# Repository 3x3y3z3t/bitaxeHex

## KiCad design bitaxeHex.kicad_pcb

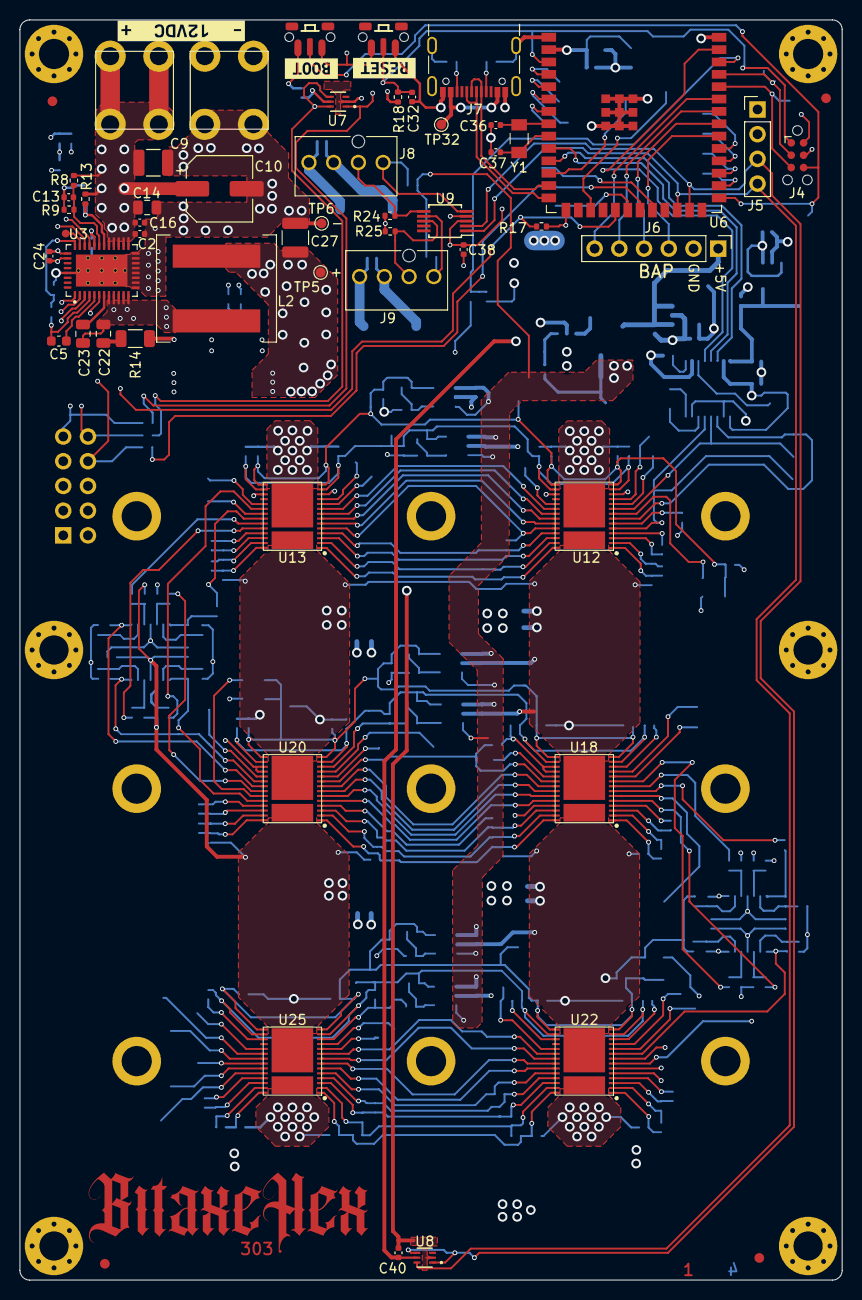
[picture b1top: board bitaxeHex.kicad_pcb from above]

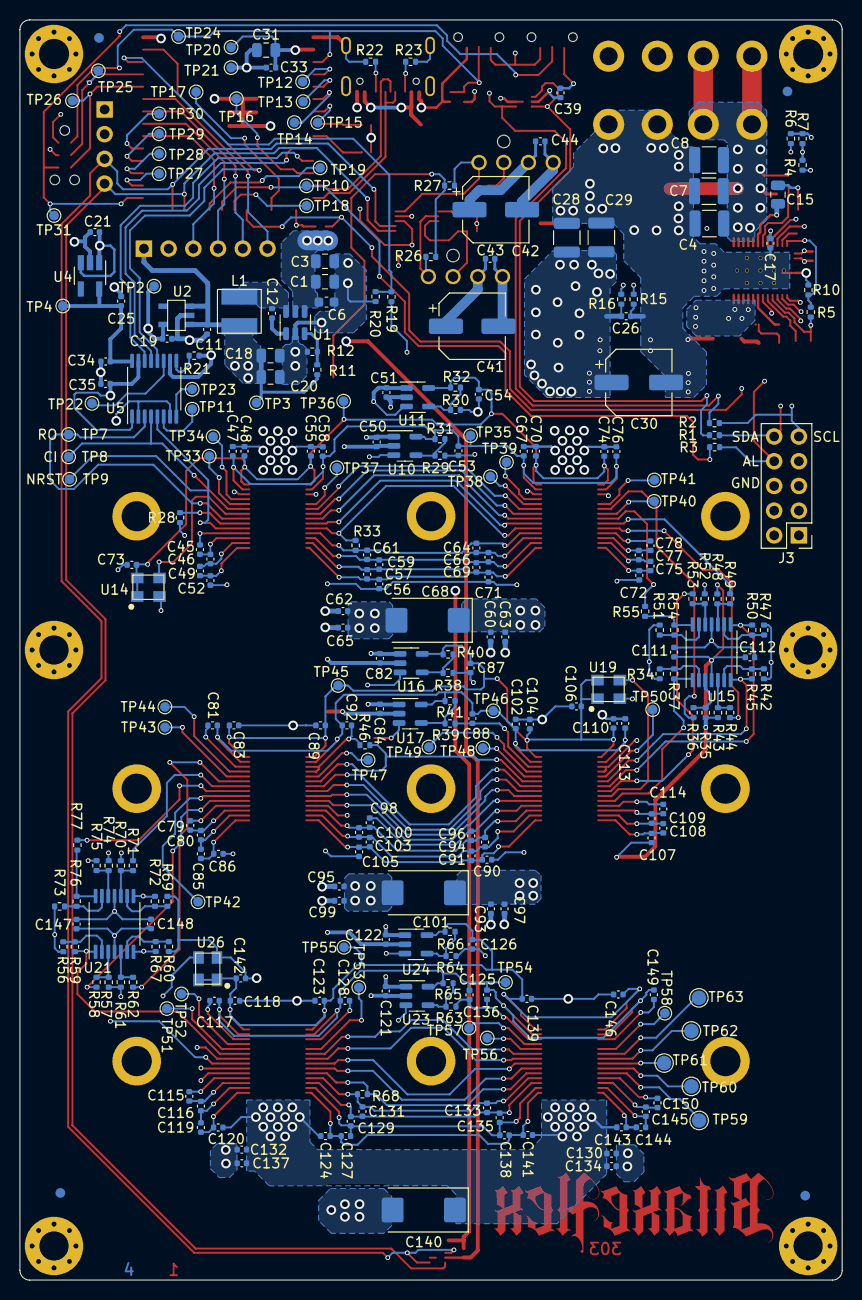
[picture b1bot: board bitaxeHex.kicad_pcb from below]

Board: 4 copper layers, 84.5 x 129.5 mm, 357 parts (283 on the bottom side), 192 nets.

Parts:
C1, C3, C18, C20, C31: 10uF; C_0805_2012Metric
C2: 4.7nF; C_0402_1005Metric
C4, C7, C8, C9: 22uF; C_1210_3225Metric
C5: 1uF; C_0603_1608Metric
C6: 0.1uF; C_0603_1608Metric
C10, C30: 180uF; CP_Elec_6.3x5.9
C11, C19, C21, C25, C32, C45, C46, C47, C48, C49, C52, C53, C54, C55, C56, C57, C58, C59, C61, C63, C64, C65, C66, C67, C69, C70, C71, C72, C74, C75, C76, C77, C78, C79, C80, C81, C83, C85, C86, C87, C88, C89, C90, C91, C92, C94, C96, C97, C98, C99, C100, C102, C103, C104, C105, C107, C108, C109, C110, C112, C113, C114, C115, C116, C117, C118, C119, C120, C123, C124, C125, C126, C127, C128, C129, C131, C133, C134, C135, C136, C137, C138, C139, C141, C143, C144, C145, C146, C148, C149, C150: 1uF; C_0402_1005Metric
C12, C33, C50, C51, C60, C62, C73, C82, C84, C93, C95, C106, C111, C121, C122, C130, C132, C142, C147: 0.1uF; C_0402_1005Metric
C13: 100nF; C_0402_1005Metric
C14, C15: 1uF; C_0805_2012Metric
C16, C26: 2.2nF; C_0402_1005Metric
C17: 4.7uF; C_0402_1005Metric
C22: 1nF; C_0805_2012Metric
C23: 100nF; C_0805_2012Metric
C24: 100pF; C_0402_1005Metric
C27, C28, C29: 47uF; C_1210_3225Metric
C34, C35, C38, C39, C40, C43, C44: 311-3342-1-ND; C_0402_1005Metric
C36, C37: 6.8pF; C_0402_1005Metric
C41, C42: 220uF; CP_Elec_6.3x7.7
C68, C101, C140: 330uF; CP_EIA-7343-31_Kemet-D_Pad2.25x2.55mm_HandSolder
FID1, FID2, FID3, FID4, FID5, FID6, FID7, FID8: Fiducial; Fiducial_1mm_Mask2mm
H1, H2, H3, H4, H5, H6: MountingHole; MountingHole_3mm_Pad_Via
H7, H8, H9, H10, H11, H12, H13, H14, H15: HeatsinkMountingHole; 3.1mm_mounting
HS1: Heatsink; hex-heatsink
J1: Screw Terminal; 7770-screw-terminal
J2: Conn_01x01; 7770-screw-terminal
J3: Conn_02x05_Odd_Even; PinHeader_2x05_P2.54mm_Vertical
J4: TC2030-IDC; Tag-Connect_TC2030-IDC-NL_2x03_P1.27mm_Vertical
J5: Conn_01x04; PinHeader_1x04_P2.54mm_Vertical
J6: Conn_01x06; PinHeader_1x06_P2.54mm_Vertical
J7: USB_C_Receptacle_USB2.0; USB_C_Receptacle_GCT_USB4105-xx-A_16P_TopMnt_Horizontal
J8, J9: Conn_01x04; 470531000
L1: 8.2 uH; 74438357082
L2: 680nH; L_Coilcraft_XAL1010-XXX
R1, R2, R3: 0R; R_0402_1005Metric
R4, R5: 17.8K; R_0402_1005Metric
R6: 10K; R_0402_1005Metric
R7: 31.6K; R_0402_1005Metric
R8: 12.7K; R_0402_1005Metric
R9, R16: 1.37K; R_0402_1005Metric
R10: 26.1K; R_0402_1005Metric
R11, R29, R30, R31, R38, R39, R41, R63, R64, R65: 115k; R_0402_1005Metric
R12, R20: 22.1k; R_0402_1005Metric
R13: 10R; R_0402_1005Metric
R14: 1R; R_1206_3216Metric
R15: 49.9R; R_0402_1005Metric
R17, R18, R26, R27, R28, R35, R36, R43, R44, R48, R49, R52, R53, R57, R58, R61, R62, R70, R71, R74, R75: 10k; R_0402_1005Metric
R19: 7.87k; R_0402_1005Metric
R21: 20k; R_0402_1005Metric
R22, R23: 5.1k; R_0402_1005Metric
R24, R25: 5.6k; R_0402_1005Metric
R32, R40, R66: 402K; R_0402_1005Metric
R33, R46, R68: 2k; R_0402_1005Metric
R34, R37, R42, R45, R47, R50, R51, R54, R55, R56, R59, R60, R67, R69, R72, R73, R76, R77: 1k; R_0402_1005Metric
SW1, SW2: SWITCH-SPST; TL3340-switch
TP1: TestPoint; TestPoint_Pad_D0.8mm
TP2, TP3, TP4, TP5, TP6, TP7, TP8, TP9, TP10, TP11, TP12, TP13, TP14, TP15, TP16, TP17, TP18, TP19, TP20, TP21, TP22, TP23, TP24, TP25, TP26, TP27, TP28, TP29, TP30, TP31, TP32, TP33, TP34, TP35, TP36, TP37, TP38, TP39, TP40, TP41, TP42, TP43, TP44, TP45, TP46, TP47, TP48, TP49, TP50, TP51, TP52, TP53, TP54, TP55, TP56, TP57, TP58: TestPoint; TestPoint_Pad_D1.0mm
TP59, TP60, TP61, TP62, TP63: TestPoint; TestPoint_Pad_D1.5mm
U1: LMR54410; SOT-23-6
U2: RT9080-33GJ5
U3: TPS546D24ARVFR; LQFN40-CLIP
U4: MIC5504; SOT-23-5_HandSoldering
U5: SN74AVC4T774; TSSOP-16_4.4x5mm_P0.65mm
U6: ESP32-S3-WROOM-1; ESP32-S3-WROOM-1U
U7, U8: TMP1075; SOT5X3-6_DRL_TEX
U9: EMC2302; MSOP-10_3x3mm_P0.5mm
U10, U11, U16, U17, U23, U24: AP7331; TSOT-23-5
U12, U13, U22, U25: BM1366_mode1; BM1366
U14, U19, U26: 25MHz; O 25,0-JO32-B-1V3-1-T1-LF
U15, U21: TLV3544; TSSOP-14_4.4x5mm_P0.65mm
U18, U20: BM1366_mode0; BM1366
Y1: 32.768kHz; SC32S-7PF20PPM
kibuzzard-65356D4E: G***; kibuzzard-65356D4E
kibuzzard-65356D5C: G***; kibuzzard-65356D5C
kibuzzard-65978662: G***; kibuzzard-65978662

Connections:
/1V8: C25.1, C34.2, TP4.1, U4.5 (VOUT), U5.16 (VCCA)
/3V3: C19.1, C21.1, C31.1, C33.1, C35.1, C38.1, C39.1, C40.1, J4.2, J5.2, R17.2, R18.1, R24.2, R25.2, TP2.1, TP20.1, U2.5 (VOUT), U4.1 (VIN), U4.3 (EN), U5.1 (DIR1), U5.15 (VCCB), U6.2 (3V3), U6.15 (GPIO3/TOUCH3/ADC1_CH2*), U7.5 (V+), U8.5 (V+), U9.3 (VDD)
/5V: C11.1, C18.1, C20.1, C50.2, C51.2, C82.2, C84.2, C121.2, C122.2, J6.1, L1.2, R11.1, R26.2, R27.2, TP3.1, U2.1 (VIN), U2.3 (EN), U10.1 (VIN), U10.3 (EN), U11.1 (VIN), U11.3 (EN), U16.1 (VIN), U16.3 (EN), U17.1 (VIN), U17.3 (EN), U23.1 (VIN), U23.3 (EN), U24.1 (VIN), U24.3 (EN)
/BM1366-1/0V8: C47.1, C53.1, C58.1, C67.1, C76.1, R31.2, TP35.1, U10.5 (VOUT), U12.13 (VDDIO_08_0), U12.16 (VDDIO_08_1), U13.13 (VDDIO_08_0), U13.16 (VDDIO_08_1)
/BM1366-1/1V8: C48.1, C54.1, C55.1, C70.1, C73.1, C74.1, R32.1, TP36.1, U11.5 (VOUT), U12.14 (VDDIO_18_0), U12.15 (VDDIO_18_1), U13.14 (VDDIO_18_0), U13.15 (VDDIO_18_1), U14.1 (EN), U14.4 (VIN)
/BM1366-1/BI1: R28.2, U12.6 (BI)
/BM1366-1/BO: R49.1, U13.23 (BO)
/BM1366-1/CLKI1: U12.8 (CLKI), U14.3 (OUT)
/BM1366-1/CO: R36.1, U13.20 (CO)
/BM1366-1/NRSTO: R44.1, U13.24 (NRSTO)
/BM1366-1/RI: R55.1, U13.22 (RI)
/BM1366-1/VDD1: C52.2, C56.1, C60.2, C62.2, C63.1, C65.1, C68.1, C71.2, C72.1, C79.1, C81.2, C82.1, C83.2, C84.1, C87.2, C88.2, C89.2, C92.2, C93.1, C95.1, C96.2, C97.2, C98.1, C99.2, C101.2, C102.2, C104.2, C106.2, C110.2, C113.2, C114.2, C147.1, C148.1, R34.2, R38.1, R39.1, R42.2, R46.1, R47.2, R51.2, R74.1, U12.29 (VDD), U13.29 (VDD), U16.2 (GND), U17.2 (GND), U18.4 (VSS), U18.12 (PLL_VSS), U18.17 (VSS), U18.18 (PIN_MODE), U18.25 (VSS), U18.30 (VSS), U19.2 (GND), U20.4 (VSS), U20.12 (PLL_VSS), U20.17 (VSS), U20.18 (PIN_MODE), U20.25 (VSS), U20.30 (VSS), U21.11 (V-)
/BM1366-2/0V8: C81.1, C88.1, C92.1, C102.1, C113.1, R41.2, TP46.1, U17.5 (VOUT), U18.13 (VDDIO_08_0), U18.16 (VDDIO_08_1), U20.13 (VDDIO_08_0), U20.16 (VDDIO_08_1)
/BM1366-2/1V8: C83.1, C87.1, C89.1, C104.1, C106.1, C110.1, R40.1, TP45.1, U16.5 (VOUT), U18.14 (VDDIO_18_0), U18.15 (VDDIO_18_1), U19.1 (EN), U19.4 (VIN), U20.14 (VDDIO_18_0), U20.15 (VDDIO_18_1)
/BM1366-2/BI2: R50.1, U15.8, U20.21 (BI)
/BM1366-2/BO: R71.1, U18.8 (BO)
/BM1366-2/CI2: R37.1, U15.1, U20.24 (CI)
/BM1366-2/CLKI2: U19.3 (OUT), U20.23 (CLKI)
/BM1366-2/CO: R58.1, U18.5 (CO)
/BM1366-2/NRSTI2: R45.1, U15.7, U20.20 (NRSTI)
/BM1366-2/NRSTO: R62.1, U18.9 (NRSTO)
/BM1366-2/RI: R77.1, U18.7 (RI)
/BM1366-2/RO2: R53.1, U20.22 (RO)
/BM1366-2/VDD2: C86.2, C90.1, C93.2, C95.2, C97.1, C99.1, C101.1, C105.2, C107.1, C111.2, C112.2, C115.1, C117.2, C118.2, C121.1, C122.1, C123.2, C125.2, C126.2, C128.2, C130.1, C131.2, C132.1, C133.1, C134.2, C136.2, C137.2, C139.2, C140.2, C142.2, C146.2, C149.2, C150.2, R35.2, R43.1, R48.1, R56.2, R60.2, R63.1, R64.1, R68.1, R69.2, R73.2, U15.4 (V+), U18.29 (VDD), U20.29 (VDD), U22.4 (VSS), U22.12 (PLL_VSS), U22.17 (VSS), U22.25 (VSS), U22.30 (VSS), U23.2 (GND), U24.2 (GND), U25.4 (VSS), U25.12 (PLL_VSS), U25.17 (VSS), U25.25 (VSS), U25.30 (VSS), U26.2 (GND)
/BM1366-3/0V8: C117.1, C125.1, C128.1, C136.1, C149.1, R65.2, TP54.1, U22.13 (VDDIO_08_0), U22.16 (VDDIO_08_1), U23.5 (VOUT), U25.13 (VDDIO_08_0), U25.16 (VDDIO_08_1)
/BM1366-3/1V8: C118.1, C123.1, C126.1, C139.1, C142.1, C146.1, R66.1, TP55.1, U22.14 (VDDIO_18_0), U22.15 (VDDIO_18_1), U24.5 (VOUT), U25.14 (VDDIO_18_0), U25.15 (VDDIO_18_1), U26.1 (EN), U26.4 (VIN)
/BM1366-3/BI3: R72.1, U21.8, U22.6 (BI)
/BM1366-3/BO3: TP60.1, U25.23 (BO)
/BM1366-3/CI3: R59.1, U21.1, U22.9 (CI)
/BM1366-3/CLKI3: U22.8 (CLKI), U26.3 (OUT)
/BM1366-3/CLKO3: TP62.1, U25.21 (CLKO)
/BM1366-3/CO3: TP63.1, U25.20 (CO)
/BM1366-3/NRSTI3: R67.1, U21.7, U22.5 (NRSTI)
/BM1366-3/NRSTO3: TP59.1, U25.24 (NRSTO)
/BM1366-3/RI3: TP61.1, U25.22 (RI)
/BM1366-3/RO3: R75.1, U22.7 (RO)
/CI: TP8.1, U5.4 (A2), U12.9 (CI)
/ESP32/ASIC_RST: U5.12 (B3), U6.39 (GPIO1/TOUCH1/ADC1_CH0)
/ESP32/EN: C32.1, J4.1, R18.2, SW1.2, TP24.1, U6.3 (EN)
/ESP32/ESP32_RX: U5.14 (B1), U6.11 (GPIO18/U1RXD/ADC2_CH7/CLK_OUT3)
/ESP32/ESP32_TX: U5.13 (B2), U6.10 (GPIO17/U1TXD/ADC2_CH6)
/ESP32/IO0: J4.6, SW2.2, TP31.1, U6.27 (GPIO0/BOOT*)
/ESP32/P_RX: J4.5, TP26.1, U6.36 (U0RXD/GPIO44/CLK_OUT2)
/ESP32/P_TX: J4.3, TP25.1, U6.37 (U0TXD/GPIO43/CLK_OUT1)
/ESP32/VDD_SAMPLE: R19.1, R20.2, U6.38 (GPIO2/TOUCH2/ADC1_CH1)
/ESP32/XIN32: C36.1, U6.8 (GPIO15/U0RTS/ADC2_CH4/XTAL_32K_P), Y1.1
/ESP32/XOUT32: C37.1, U6.9 (GPIO16/U0CTS/ADC2_CH5/XTAL_32K_NH5), Y1.2
/Fan/FAN1_PWM: J8.4, R27.1, U9.5 (PWM1)
/Fan/FAN1_TACH: J8.3, R24.1, U9.6 (TACH1)
/Fan/FAN2_PWM: J9.4, R26.1, U9.7 (PWM2)
/Fan/FAN2_TACH: J9.3, R25.1, U9.8 (TACH2)
/NRSTI: TP9.1, U5.5 (A3), U12.5 (NRSTI)
/Power/AGND: C13.2, C15.1, R6.1, R7.2, R9.2, R10.2, U3.37 (AGND)
/Power/PGOOD: R17.1, U3.1 (PGD), U6.19 (GPIO11/TOUCH11/ADC2_CH0/FSPID/FSPIIO5/S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)
/Power/PMB_ALRT: J3.8, R3.2, U3.6 (SMB_ALRT)
/Power/PMB_SCL: J3.9, R2.2, U3.3 (PMB_CLK)
/Power/PMB_SDA: J3.10, R1.2, U3.2 (PMB_DATA)
/Power/SW: C22.1, C23.2, L2.1, U3.8 (SW), U3.9 (SW), U3.10 (SW), U3.11 (SW), U3.12 (SW)
/RO: TP7.1, U5.3 (A1), U12.7 (RO)
/SCL: J5.3, R2.1, U6.25 (GPIO48/SPICLK_N/SUBSPICLK_N_DIFF), U7.1 (SCL), U8.1 (SCL), U8.4 (A0), U9.2 (SMCLK)
/SDA: J5.4, R1.1, U6.24 (GPIO47/SPICLK_P/SUBSPICLK_P_DIFF), U7.4 (A0), U7.6 (SDA), U8.6 (SDA), U9.1 (SMDATA)
/SMB_ALRT: R3.1, TP10.1, U6.21 (GPIO13/TOUCH13/ADC2_CH2/FSPIQ/FSPIIO7/S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)
/VDD: C26.1, C27.1, C28.1, C29.1, C30.1, C120.2, C124.1, C130.2, C132.2, C134.1, C137.1, C140.1, C141.2, C143.1, C147.2, C148.2, L2.2, R16.1, R19.2, R57.1, R61.1, R70.1, TP5.1, U21.4 (V+), U22.29 (VDD), U25.29 (VDD)
/VIN: C1.1, C2.1, C3.1, C4.1, C6.2, C7.1, C8.1, C9.1, C10.1, C14.1, C16.1, C41.1, C42.1, C43.1, C44.1, J1.1, J8.2, J9.2, R8.1, R13.1, U1.4 (EN), U1.5 (VIN), U3.21 (PVIN), U3.22 (PVIN), U3.23 (PVIN), U3.24 (PVIN), U3.25 (PVIN)
GND: C1.2, C2.2, C3.2, C4.2, C6.1, C7.2, C8.2, C9.2, C10.2, C11.2, C14.2, C16.2, C17.2, C18.2, C19.2, C20.2, C21.2, C25.2, C26.2, C27.2, C28.2, C29.2, C30.2, C31.2, C32.2, C33.2, C34.1, C35.2, C36.2, C37.2, C38.2, C39.2, C40.2, C41.2, C42.2, C43.2, C44.2, C45.1, C47.2, C48.2, C50.1, C51.1, C53.2, C54.2, C55.2, C58.2, C60.1, C61.2, C62.1, C63.2, C64.1, C65.2, C67.2, C68.2, C70.2, C73.2, C74.2, C76.2, C78.2, C111.1, C112.1, H1.1, H2.1, J2.1, J3.6, J4.4, J5.1, J6.2, J7.A1 (GND), J7.A12 (GND), J7.B1 (GND), J7.B12 (GND), J7.S1 (SHIELD), J8.1, J9.1, R12.2, R14.2, R15.2, R20.1, R21.1, R22.1, R23.1, R28.1, R29.1, R30.1, R33.1, R52.1, SW1.1, SW2.1, TP6.1, TP21.1, U1.2 (GND), U2.2 (GND), U3.13 (PGND), U3.14 (PGND), U3.15 (PGND), U3.16 (PGND), U3.17 (PGND), U3.18 (PGND), U3.19 (PGND), U3.20 (PGND), U3.41 (PAD), U4.2 (GND), U5.2 (DIR2), U5.7 (DIR3), U5.10 (GND), U6.1 (GND), U6.40 (GND), U6.41 (GND), U7.2 (GND), U8.2 (GND), U9.4 (GND), U10.2 (GND), U11.2 (GND), U12.4 (VSS), U12.12 (PLL_VSS), U12.17 (VSS), U12.25 (VSS), U12.30 (VSS), U13.4 (VSS), U13.12 (PLL_VSS), U13.17 (VSS), U13.25 (VSS), U13.30 (VSS), U14.2 (GND), U15.11 (V-)
unnamed: C22.2, R14.1
unnamed: J6.3, U6.32 (MTCK/GPIO39/CLK_OUT3/SUBSPICS1)
unnamed: J6.4, U6.33 (MTDO/GPIO40/CLK_OUT2)
unnamed: J6.5, U6.34 (MTDI/GPIO41/CLK_OUT1)
unnamed: J6.6, U6.35 (MTMS/GPIO42)
unnamed: J7.A5 (CC1), R22.2
unnamed: J7.B5 (CC2), R23.2
unnamed: J7.A4 (VBUS), J7.A9 (VBUS), J7.B4 (VBUS), J7.B9 (VBUS), TP32.1
unnamed: R54.1, R55.2, U15.14
unnamed: R76.1, R77.2, U21.14
unnamed: C12.2, U1.1 (CB)
unnamed: R11.2, R12.1, U1.3 (FB)
unnamed: C12.1, L1.1, U1.6 (SW)
unnamed: TP1.1, U3.31 (ADRSEL)
unnamed: C15.2, R13.2, U3.26 (AVIN)
unnamed: C23.1, U3.7 (BOOT)
unnamed: C5.1, R4.1, R5.1, U3.4 (BP1V5)
unnamed: C5.2, U3.5 (DRTN)
unnamed: C13.1, R8.2, R9.1, U3.27 (EN/UVLO)
unnamed: C24.2, R15.1, U3.34 (GOSNS)
unnamed: R5.2, R10.1, U3.32 (MSEL1)
unnamed: R6.2, U3.29 (MSEL2)
unnamed: C17.1, U3.28 (VDD5)
unnamed: C24.1, R16.2, U3.33 (VOSNS)
unnamed: R4.2, R7.1, U3.30 (VSEL)
unnamed: TP11.1, U5.6 (A4)
unnamed: TP22.1, U5.11 (B4)
unnamed: TP23.1, U5.8 (DIR4)
unnamed: R21.2, U5.9 (OE)
unnamed: TP12.1, U6.4 (GPIO4/TOUCH4/ADC1_CH3)
unnamed: TP13.1, U6.5 (GPIO5/TOUCH5/ADC1_CH4)
unnamed: TP14.1, U6.6 (GPIO6/TOUCH6/ADC1_CH5)
unnamed: TP15.1, U6.7 (GPIO7/TOUCH7/ADC1_CH6)
unnamed: TP16.1, U6.12 (GPIO8/TOUCH8/ADC1_CH7/SUBSPICS1)
unnamed: TP17.1, U6.17 (GPIO9/TOUCH9/ADC1_CH8/FSPIHD/SUBSPIHD)
unnamed: TP18.1, U6.20 (GPIO12/TOUCH12/ADC2_CH1/FSPICLK/FSPIIO6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)
unnamed: TP19.1, U6.22 (GPIO14/TOUCH14/ADC2_CH3/FSPIWP/FSPIDQS/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)
unnamed: J7.A7 (D-), J7.B7 (D-), U6.13 (GPIO19/U1RTS/ADC2_CH8/CLK_OUT2/USB_D-)
unnamed: J7.A6 (D+), J7.B6 (D+), U6.14 (GPIO20/U1CTS/ADC2_CH9/CLK_OUT1/USB_D+)
unnamed: TP30.1, U6.31 (GPIO38/FSPIWP/SUBSPIWP)
unnamed: TP29.1, U6.30 (SPIDQS/GPIO37/FSPIQ/SUBSPIQ)
unnamed: TP27.1, U6.28 (SPIIO6/GPIO35/FSPID/SUBSPID)
unnamed: TP28.1, U6.29 (SPIIO7/GPIO36/FSPICLK/SUBSPICLK)
unnamed: R29.2, R31.1, U10.4 (ADJ)
unnamed: R30.2, R32.2, U11.4 (ADJ)
unnamed: TP33.1, U12.10 (ADDR0)
unnamed: TP34.1, U12.11 (ADDR1)
unnamed: U12.23 (BO), U13.6 (BI)
unnamed: U12.21 (CLKO), U13.8 (CLKI)
unnamed: U12.20 (CO), U13.9 (CI)
unnamed: TP37.1, U12.19 (INV_CLKO)
unnamed: R33.2, U12.24 (NRSTO), U13.5 (NRSTI)
unnamed: U12.22 (RI), U13.7 (RO)
unnamed: C49.2, C52.1, U12.1 (VDD1_0)
unnamed: C56.2, C57.1, C69.2, C71.1, U12.28 (VDD1_1), U13.1 (VDD1_0)
unnamed: C46.2, C49.1, U12.2 (VDD2_0)
unnamed: C57.2, C59.1, C66.2, C69.1, U12.27 (VDD2_1), U13.2 (VDD2_0)
unnamed: C45.2, C46.1, U12.3 (VDD3_0)
unnamed: C59.2, C61.1, C64.2, C66.1, U12.26 (VDD3_1), U13.3 (VDD3_0)
unnamed: TP38.1, U13.10 (ADDR0)
unnamed: TP39.1, U13.11 (ADDR1)
unnamed: TP40.1, U13.21 (CLKO)
unnamed: TP41.1, U13.19 (INV_CLKO)
unnamed: C72.2, C75.1, U13.28 (VDD1_1)
unnamed: C75.2, C77.1, U13.27 (VDD2_1)
unnamed: C77.2, C78.1, U13.26 (VDD3_1)
unnamed: R35.1, R36.2, U15.3 (+)
unnamed: R34.1, R37.2, U15.2 (-)
unnamed: R43.2, R44.2, U15.5 (+)
unnamed: R42.1, R45.2, U15.6 (-)
unnamed: R48.2, R49.2, U15.10 (+)
unnamed: R47.1, R50.2, U15.9 (-)
unnamed: R52.2, R53.2, U15.12 (+)
unnamed: R51.1, R54.2, U15.13 (-)
unnamed: R38.2, R40.2, U16.4 (ADJ)
unnamed: R39.2, R41.1, U17.4 (ADJ)
unnamed: TP43.1, U18.10 (ADDR0)
unnamed: TP44.1, U18.11 (ADDR1)
unnamed: U18.21 (BI), U20.8 (BO)
unnamed: U18.24 (CI), U20.5 (CO)
unnamed: U18.23 (CLKI), U20.6 (CLKO)
unnamed: TP42.1, U18.6 (CLKO)
unnamed: TP47.1, U18.19 (INV_CLKO)
unnamed: R46.2, U18.20 (NRSTI), U20.9 (NRSTO)
unnamed: U18.22 (RO), U20.7 (RI)
unnamed: C79.2, C80.1, U18.3 (VDD1_0)
unnamed: C94.2, C96.1, C98.2, C100.1, U18.26 (VDD1_1), U20.3 (VDD1_0)
unnamed: C80.2, C85.1, U18.2 (VDD2_0)
unnamed: C91.2, C94.1, C100.2, C103.1, U18.27 (VDD2_1), U20.2 (VDD2_0)
unnamed: C85.2, C86.1, U18.1 (VDD3_0)
unnamed: C90.2, C91.1, C103.2, C105.1, U18.28 (VDD3_1), U20.1 (VDD3_0)
unnamed: TP48.1, U20.10 (ADDR0)
unnamed: TP49.1, U20.11 (ADDR1)
unnamed: TP50.1, U20.19 (INV_CLKO)
unnamed: C109.2, C114.1, U20.26 (VDD1_1)
unnamed: C108.2, C109.1, U20.27 (VDD2_1)
unnamed: C107.2, C108.1, U20.28 (VDD3_1)
unnamed: R57.2, R58.2, U21.3 (+)
unnamed: R56.1, R59.2, U21.2 (-)
unnamed: R61.2, R62.2, U21.5 (+)
unnamed: R60.1, R67.2, U21.6 (-)
unnamed: R70.2, R71.2, U21.10 (+)
unnamed: R69.1, R72.2, U21.9 (-)
unnamed: R74.2, R75.2, U21.12 (+)
unnamed: R73.1, R76.2, U21.13 (-)
unnamed: TP51.1, U22.10 (ADDR0)
unnamed: TP52.1, U22.11 (ADDR1)
unnamed: U22.23 (BO), U25.6 (BI)
unnamed: U22.21 (CLKO), U25.8 (CLKI)
unnamed: U22.20 (CO), U25.9 (CI)
unnamed: TP53.1, U22.19 (INV_CLKO)
unnamed: R68.2, U22.24 (NRSTO), U25.5 (NRSTI)
unnamed: U22.22 (RI), U25.7 (RO)
unnamed: C119.2, C120.1, U22.1 (VDD1_0)
unnamed: C124.2, C127.1, C138.2, C141.1, U22.28 (VDD1_1), U25.1 (VDD1_0)
unnamed: C116.2, C119.1, U22.2 (VDD2_0)
unnamed: C127.2, C129.1, C135.2, C138.1, U22.27 (VDD2_1), U25.2 (VDD2_0)
unnamed: C115.2, C116.1, U22.3 (VDD3_0)
unnamed: C129.2, C131.1, C133.2, C135.1, U22.26 (VDD3_1), U25.3 (VDD3_0)
unnamed: R63.2, R65.1, U23.4 (ADJ)
unnamed: R64.2, R66.2, U24.4 (ADJ)
unnamed: TP56.1, U25.10 (ADDR0)
unnamed: TP57.1, U25.11 (ADDR1)
unnamed: TP58.1, U25.19 (INV_CLKO)
unnamed: C143.2, C144.1, U25.28 (VDD1_1)
unnamed: C144.2, C145.1, U25.27 (VDD2_1)
unnamed: C145.2, C150.1, U25.26 (VDD3_1)

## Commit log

2024-03-26 Move logo to F.Cu layer
